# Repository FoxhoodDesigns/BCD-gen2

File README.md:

# Binary Clock 2
A successor to my very first electronics project i made when I was 16y old: A Binary Clock using only discrete logic (4000/74HC series)
Re-imagined using the skills I learned over time to turn it from a barely working beginner's project. To something I honestly could sell as a Soldering Kit.
Complete with fully worked out Power design that can safely be run off a Li-Ion Battery.

For more information. Please visit the Hackaday IO journal that is being written alongside this project that goes into depth on the reverse engineering of the original and iterating on its design:
https://hackaday.io/project/197273-4000-series-bcd-clock-g2

# NOTE ON PCB Layout:
This project is designed to be a little more artistic in appearance with the PCB visible to the outside world.
As such the PCB is intended to be made using a transparent Solder-mask that renders the copper visible. With the Front side lacking a Copper-pour and using rounded traces.
Please refer to OSH-Park's "After Dark" service for examples on how such PCBs tend to look.

# Current Status:
Still in mid Layout. Though should be ready for having its first set built once I finish it. Trying to figure out what to do with the Blank spot on the front in regards of copper. Maybe A Image of some kind?

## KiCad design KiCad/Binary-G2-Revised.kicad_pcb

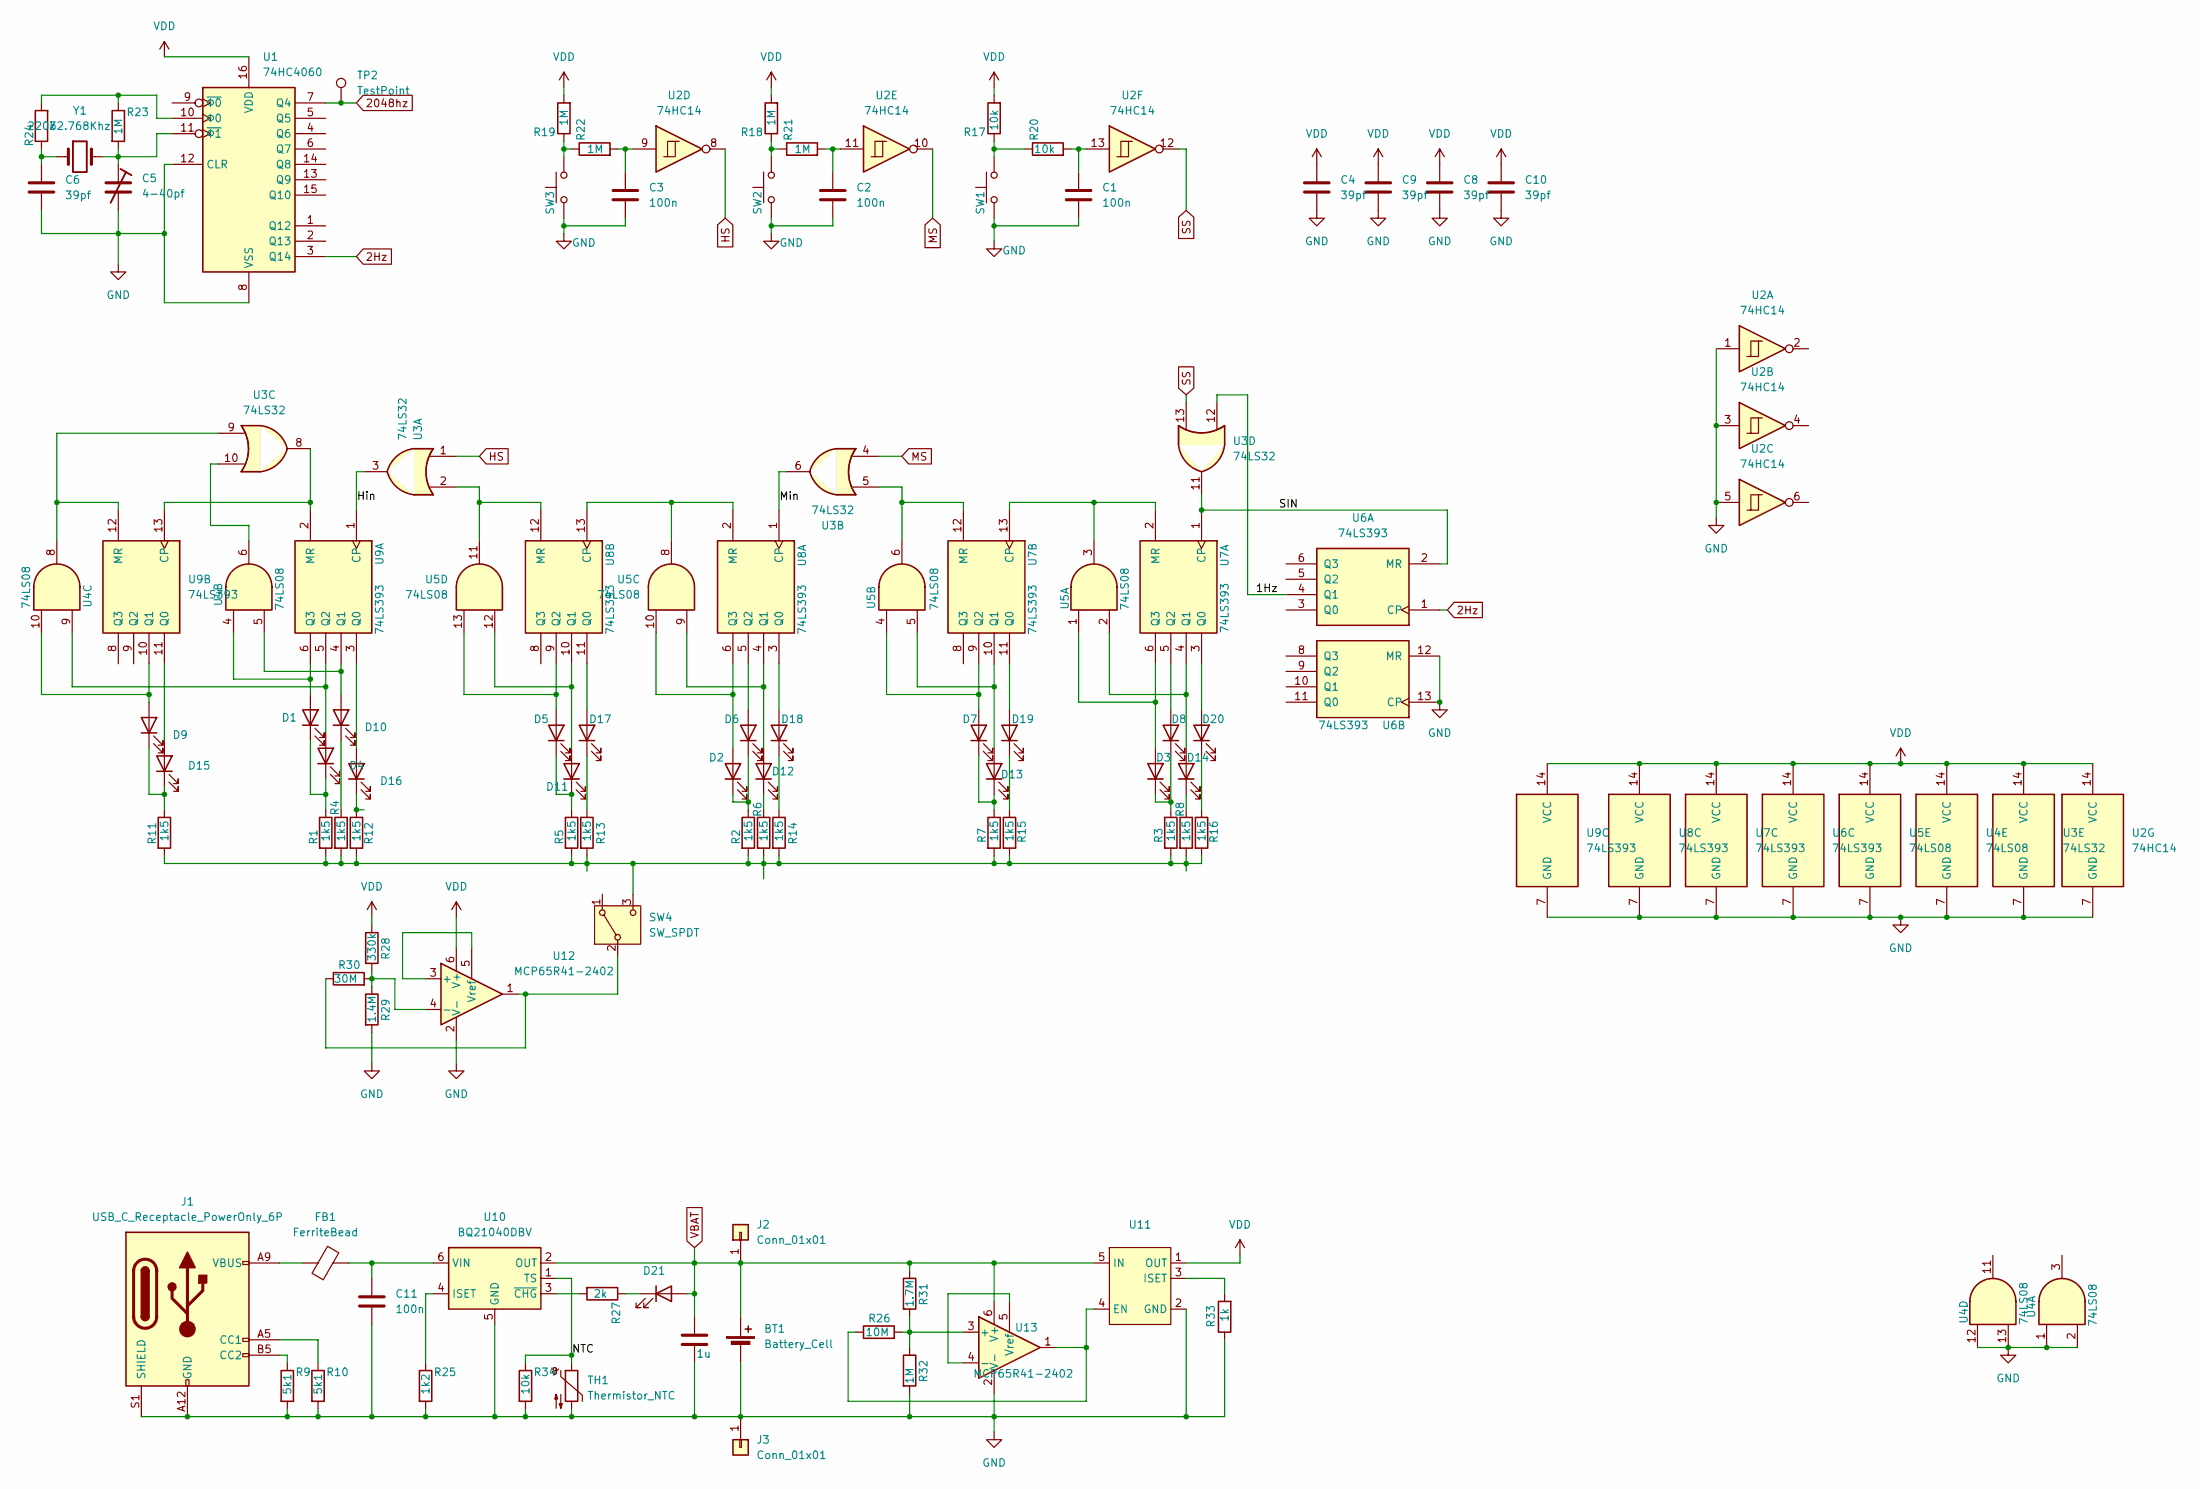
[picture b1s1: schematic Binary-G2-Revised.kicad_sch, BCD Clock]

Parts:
BT1: Battery_Cell
C1, C2, C3, C11: 100n; C_0805_2012Metric_Pad1.18x1.45mm_HandSolder
C4, C6, C8, C9, C10: 39pf; C_0805_2012Metric_Pad1.18x1.45mm_HandSolder
C5: 4-40pf; C_Trimmer_Murata_TZY2
C7: 1u; C_0805_2012Metric_Pad1.18x1.45mm_HandSolder
D1, D2, D3, D4, D5, D6, D7, D8, D9, D10, D11, D12, D13, D14, D15, D16, D17, D18, D19, D20: LED; LED_1206_3216Metric_Pad1.42x1.75mm_HandSolder
D21: LED; LED_0805_2012Metric_Pad1.15x1.40mm_HandSolder
FB1: FerriteBead; L_0805_2012Metric_Pad1.15x1.40mm_HandSolder
J1: USB_C_Receptacle_PowerOnly_6P; USB_C_Receptacle_USB4130
J2, J3: Conn_01x01; SolderWirePad_1x01_SMD_1x2mm
R1, R2, R3, R4, R5, R6, R7, R8, R11, R12, R13, R14, R15, R16: 1k5; R_0805_2012Metric_Pad1.20x1.40mm_HandSolder
R9, R10: 5k1; R_0805_2012Metric_Pad1.20x1.40mm_HandSolder
R17, R20, R34: 10k; R_0805_2012Metric_Pad1.20x1.40mm_HandSolder
R18, R19, R21, R22, R23, R32: 1M; R_0805_2012Metric_Pad1.20x1.40mm_HandSolder
R24: 220k; R_0805_2012Metric_Pad1.20x1.40mm_HandSolder
R25: 1k2; R_0805_2012Metric_Pad1.20x1.40mm_HandSolder
R26: 10M; R_0805_2012Metric_Pad1.20x1.40mm_HandSolder
R27: 2k; R_0805_2012Metric_Pad1.20x1.40mm_HandSolder
R28: 330k; R_0805_2012Metric_Pad1.20x1.40mm_HandSolder
R29: 1.4M; R_0805_2012Metric_Pad1.20x1.40mm_HandSolder
R30: 30M; R_0805_2012Metric_Pad1.20x1.40mm_HandSolder
R31: 1.7M; R_0805_2012Metric_Pad1.20x1.40mm_HandSolder
R33: 1k; R_0805_2012Metric_Pad1.20x1.40mm_HandSolder
SW1, SW2, SW3: PTH_RA_7.4x4.3mm; SW_Push_1P1T_NO_Vertical_Wuerth_434133025816
SW4: SW_SPDT; SW_SPDT_PCM12
TH1: Thermistor_NTC; SolderWirePad_1x01_SMD_1x2mm
TP2: TestPoint; TestPoint_Pad_2.0x2.0mm
U1: 74HC4060; SO-16_3.9x9.9mm_P1.27mm
U2: 74HC14; SO-14_3.9x8.65mm_P1.27mm
U3: 74LS32; SO-14_3.9x8.65mm_P1.27mm
U4, U5: 74LS08; SO-14_3.9x8.65mm_P1.27mm
U6, U7, U8, U9: 74LS393; SO-14_3.9x8.65mm_P1.27mm
U10: BQ21040DBV; SOT-23-6
U11: SOT-23-5_HandSoldering
U12, U13: MCP65R41-2402; SOT-23-6
Y1: 32.768Khz; Crystal_C26-LF_D2.1mm_L6.5mm_Horizontal_1EP_style2

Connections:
2Hz: U1.3 (Q14), U6.1 (CP)
2048hz: TP2.1, U1.7 (Q4)
/1Hz: U3.12, U6.4 (Q1)
/Hin: U3.3, U9.1 (CP)
/Min: U3.6, U8.1 (CP)
/NTC: R34.1, TH1.1, U10.1 (TS)
/SIN: U3.11, U6.2 (MR), U7.1 (CP)
GND: BT1.2 (-), C1.2, C2.2, C3.2, C4.2, C5.2, C6.2, C7.2, C8.2, C9.2, C10.2, C11.2, J1.A12 (GND), J1.B12 (GND), J1.S1 (SHIELD), J3.1, R9.2, R10.2, R25.2, R29.2, R32.2, R33.1, R34.2, SW1.1, SW2.1, SW3.1, TH1.2, U1.8 (VSS), U1.12 (CLR), U2.1, U2.3, U2.5, U2.7 (GND), U3.7 (GND), U4.1, U4.2, U4.7 (GND), U4.12, U4.13, U5.7 (GND), U6.7 (GND), U6.12 (MR), U6.13 (CP), U7.7 (GND), U8.7 (GND), U9.7 (GND), U10.5 (GND), U11.2 (GND), U12.2 (V-), U13.2 (V-)
HS: U2.8, U3.1
MS: U2.10, U3.4
unnamed: C1.1, R20.2, U2.13
unnamed: C2.1, R21.2, U2.11
unnamed: C3.1, R22.2, U2.9
unnamed: C6.1, R24.1, Y1.1
unnamed: D1.2 (A), U4.4, U9.6 (Q3)
unnamed: D1.1 (K), D4.1 (K), R1.1
unnamed: D2.2 (A), U5.10, U8.6 (Q3)
unnamed: D2.1 (K), D6.1 (K), R2.1
unnamed: D3.2 (A), U5.1, U7.6 (Q3)
unnamed: D3.1 (K), D8.1 (K), R3.1
unnamed: D4.2 (A), U4.9, U9.5 (Q2)
unnamed: D5.2 (A), U5.13, U8.9 (Q2)
unnamed: D6.2 (A), U8.5 (Q2)
unnamed: D7.2 (A), U5.4, U7.9 (Q2)
unnamed: D8.2 (A), U7.5 (Q2)
unnamed: D9.2 (A), U4.10, U9.10 (Q1)
unnamed: D10.2 (A), U4.5, U9.4 (Q1)
unnamed: D10.1 (K), R4.1
unnamed: D11.2 (A), U5.12, U8.10 (Q1)
unnamed: D5.1 (K), D11.1 (K), R5.1
unnamed: D12.2 (A), U5.9, U8.4 (Q1)
unnamed: D12.1 (K), R6.1
unnamed: D13.2 (A), U5.5, U7.10 (Q1)
unnamed: D7.1 (K), D13.1 (K), R7.1
unnamed: D14.2 (A), U5.2, U7.4 (Q1)
unnamed: D14.1 (K), R8.1
unnamed: D15.2 (A), U9.11 (Q0)
unnamed: D9.1 (K), D15.1 (K), R11.1
unnamed: D16.2 (A), U9.3 (Q0)
unnamed: D16.1 (K), R12.1
unnamed: D17.2 (A), U8.11 (Q0)
unnamed: D17.1 (K), R13.1
unnamed: D18.2 (A), U8.3 (Q0)
unnamed: D18.1 (K), R14.1
unnamed: D19.2 (A), U7.11 (Q0)
unnamed: D19.1 (K), R15.1
unnamed: D20.2 (A), U7.3 (Q0)
unnamed: D20.1 (K), R16.1
unnamed: D21.1 (K), R27.1
unnamed: FB1.1, J1.A9 (VBUS), J1.B9 (VBUS)
unnamed: J1.A5 (CC1), R10.1
unnamed: J1.B5 (CC2), R9.1
unnamed: R17.1, R20.1, SW1.2
unnamed: R18.1, R21.1, SW2.2
unnamed: R19.1, R22.1, SW3.2
unnamed: R30.1, SW4.2 (B), U12.1
unnamed: R1.2, R2.2, R3.2, R4.2, R5.2, R6.2, R7.2, R8.2, R11.2, R12.2, R13.2, R14.2, R15.2, R16.2, SW4.3 (C)
unnamed: C5.1, R23.2, U1.11 (~Φ1), Y1.2
unnamed: R23.1, R24.2, U1.10 (Φ0)
unnamed: U3.10, U4.6
unnamed: U5.3, U7.2 (MR), U7.13 (CP)
unnamed: U3.5, U5.6, U7.12 (MR)
unnamed: U5.8, U8.2 (MR), U8.13 (CP)
unnamed: U3.2, U5.11, U8.12 (MR)
unnamed: U3.8, U9.2 (MR), U9.13 (CP)
unnamed: U3.9, U4.8, U9.12 (MR)
unnamed: R25.1, U10.4 (ISET)
unnamed: C11.1, FB1.2, U10.6 (VIN)
unnamed: R27.2, U10.3 (~CHG)
unnamed: R26.1, U11.4 (EN), U13.1
unnamed: R33.2, U11.3 (ISET)
unnamed: U12.3 (+), U12.5 (Vref)
unnamed: R28.2, R29.1, R30.2, U12.4 (-)
unnamed: R26.2, R31.2, R32.1, U13.3 (+)
unnamed: U13.4 (-), U13.5 (Vref)
SS: U2.12, U3.13
VBAT: BT1.1 (+), C7.1, D21.2 (A), J2.1, R31.1, U10.2 (OUT), U11.5 (IN), U13.6 (V+)
VDD: C4.1, C8.1, C9.1, C10.1, R17.2, R18.2, R19.2, R28.1, U1.16 (VDD), U2.14 (VCC), U3.14 (VCC), U4.14 (VCC), U5.14 (VCC), U6.14 (VCC), U7.14 (VCC), U8.14 (VCC), U9.14 (VCC), U11.1 (OUT), U12.6 (V+)

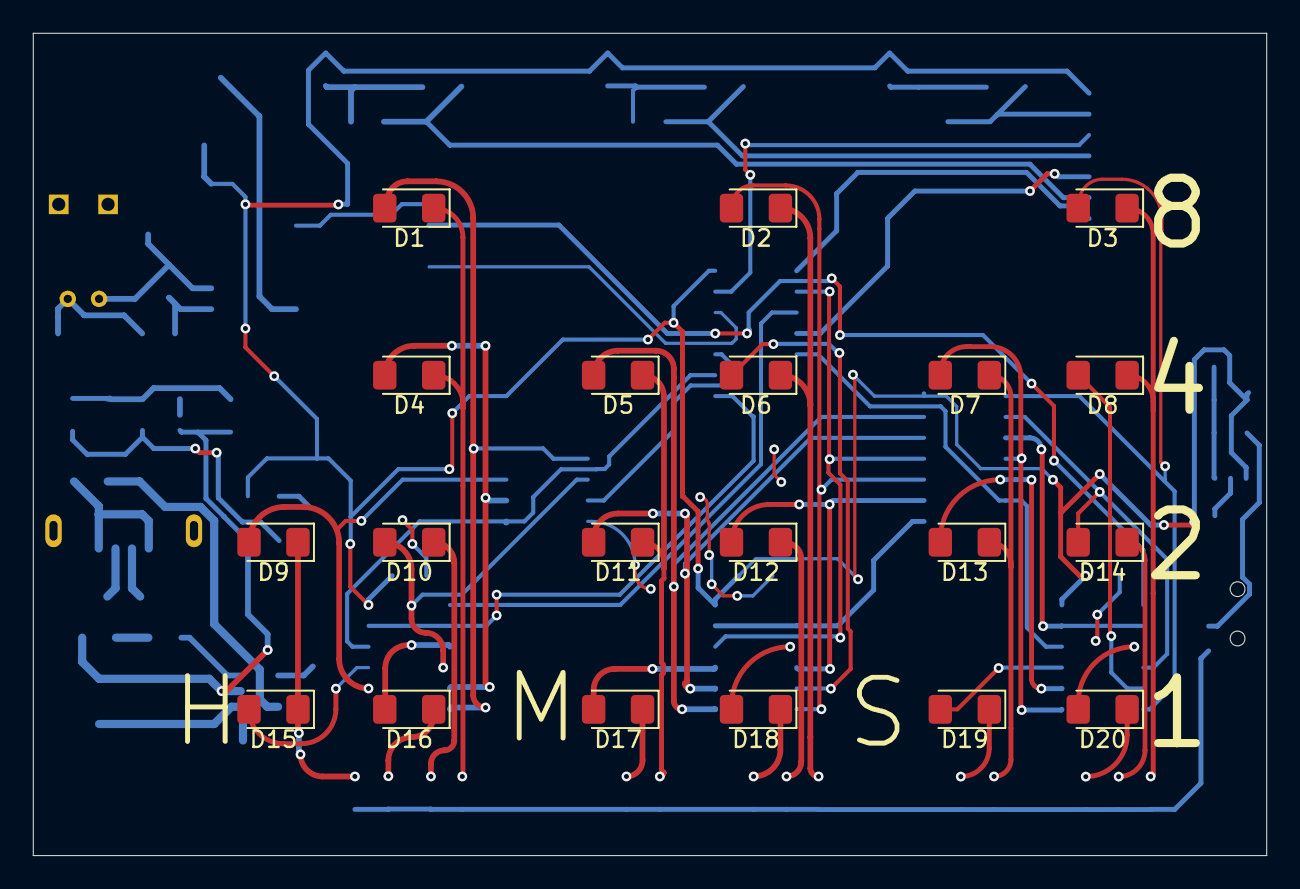
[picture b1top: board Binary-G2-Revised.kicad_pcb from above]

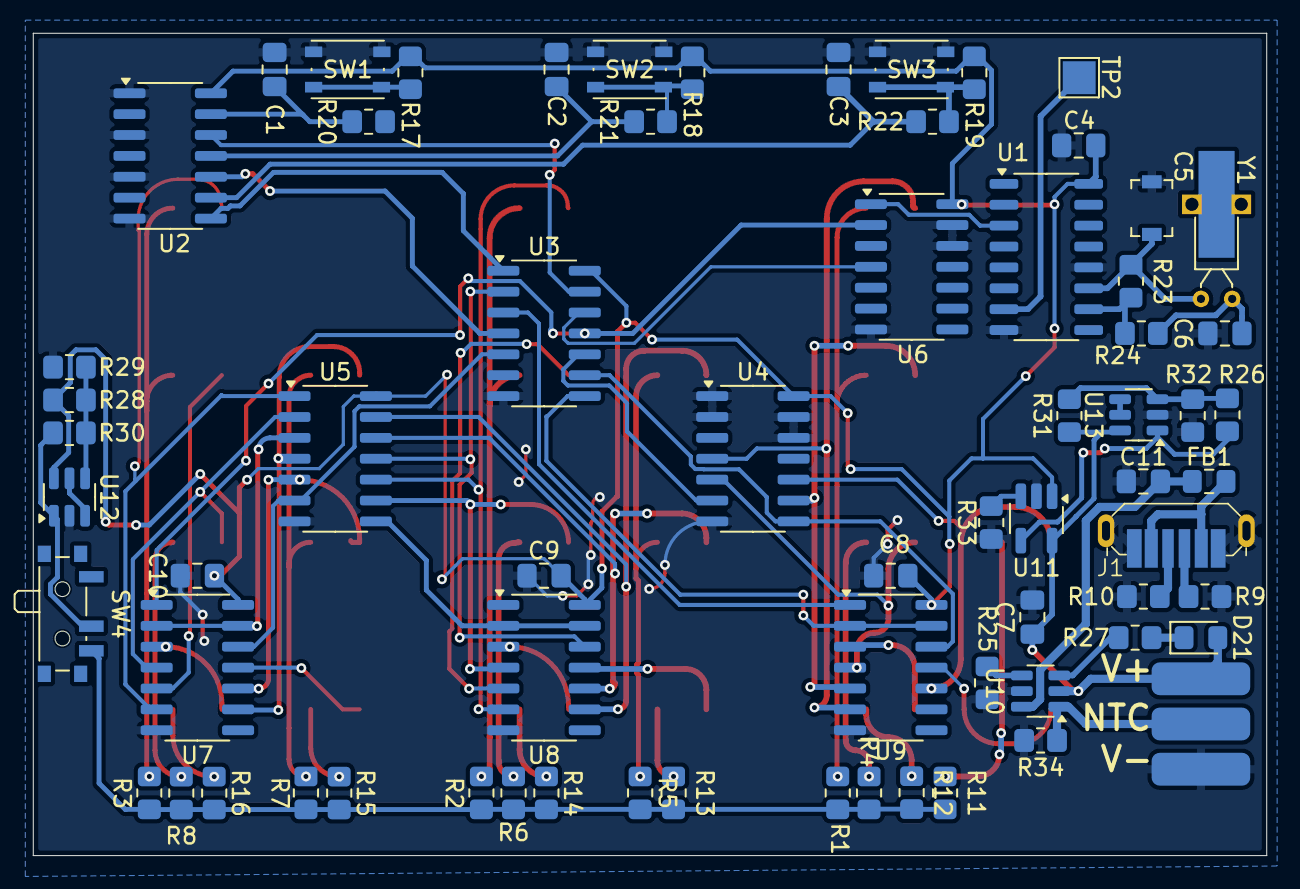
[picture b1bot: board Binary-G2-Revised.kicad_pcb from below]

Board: 2 copper layers, 75.0 x 50.0 mm, 90 parts (70 on the bottom side), 78 nets.

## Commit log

2025-02-24 Initial Upload
2025-02-24 Update with minimum layout
    Needs a lot more work.
2025-02-24 Quick Update Documentation
